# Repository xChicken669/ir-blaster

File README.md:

# 
IR blaster that runs on an esp32 c3 supermini It uses 4 push buttons, an IR led and an IR receiver
## why have I made this project??
I have always wanted to make an IR blaster from scratch but I didnt have the time and money to do so, now I am able to make it thanks to hackclub :).
## how did I make this project
- Autodesk Fusion 360 for CAD
- Kicad for pcb design
- Arduino IDE for firmware
## screenshots

also it uses two m2 screws for assembly and two m2 nuts.

## BOM
| Component                      | Qty | Link                                                                               | Price - CZK | Price  - USD |
|--------------------------------|-----|------------------------------------------------------------------------------------|-------------|--------------|
|  VISHAY TSAL6100 IR LED        | 1   | https://www.gme.cz/v/1486297/vishay-tsal6100-infracervena-led-5mm                  | 5           | 0.23         |
| DIOTEC BC337                   | 1   | https://www.gme.cz/v/1487096/diotec-bc337-40bk-bipolarni-tranzistor                | 0.85        | 0.0391       |
| Resistor 150ohms               | 1   | https://www.gme.cz/v/1494168/gym-cym-rm-150r-06w-1-0207-metalizovany-rezistor      | 4           | 0.184        |
| Resistor 1000ohms              | 1   | https://www.gme.cz/v/1486228/gym-cym-rm-1k-06w-1-0207-metalizovany-rezistor        | 4           | 0.184        |
| Esp32 C3 Supermini             | 1   | https://www.laskakit.cz/esp32-c3-super-mini-wifi-bluetooth-modul/                  | 148         | 6.808        |
| VISHAY TSOP3848 IR RECEIVER    | 1   | https://www.gme.cz/v/1489884/vishay-tsop4838-ir-prijimac                           | 18          | 0.828        |
| KLS TS6601-5.0-100 push button | 4   | https://www.gme.cz/v/1500825/kls-ts6601-50-100-mikrospinac                         | 2.8         | 0.1288       |
| 0.96" I2C OLED display 128x64  | 1   | https://www.gme.cz/v/1509095/oled-displej-096-128x64-i2c-bily                      | 100         | 4.6          |
| LiPol Battery                  | 1   | https://www.laskakit.cz/geb-lipol-baterie-302040-200mah-3-7v-jst-sh-2-0/#ratingTab | 70          | 3.22         |
| Tp4056 Battery charging module | 1   | https://www.laskakit.cz/nabijecka-li-ion-clanku-tp4056-s-ochranou-usb-c/           | 18          | 0.828        |
| PCB                            | 5   | https://jlcpcb.com                                                                 | 226.3043478 | 10.41        |
| Filament                       | 12g | Supplied by myself                                                                 | 4.8         | 0.2208       |

total = 601.75czk / 27.56usd
## AI
I used ai for a little bit of research for coding and for finding correct components

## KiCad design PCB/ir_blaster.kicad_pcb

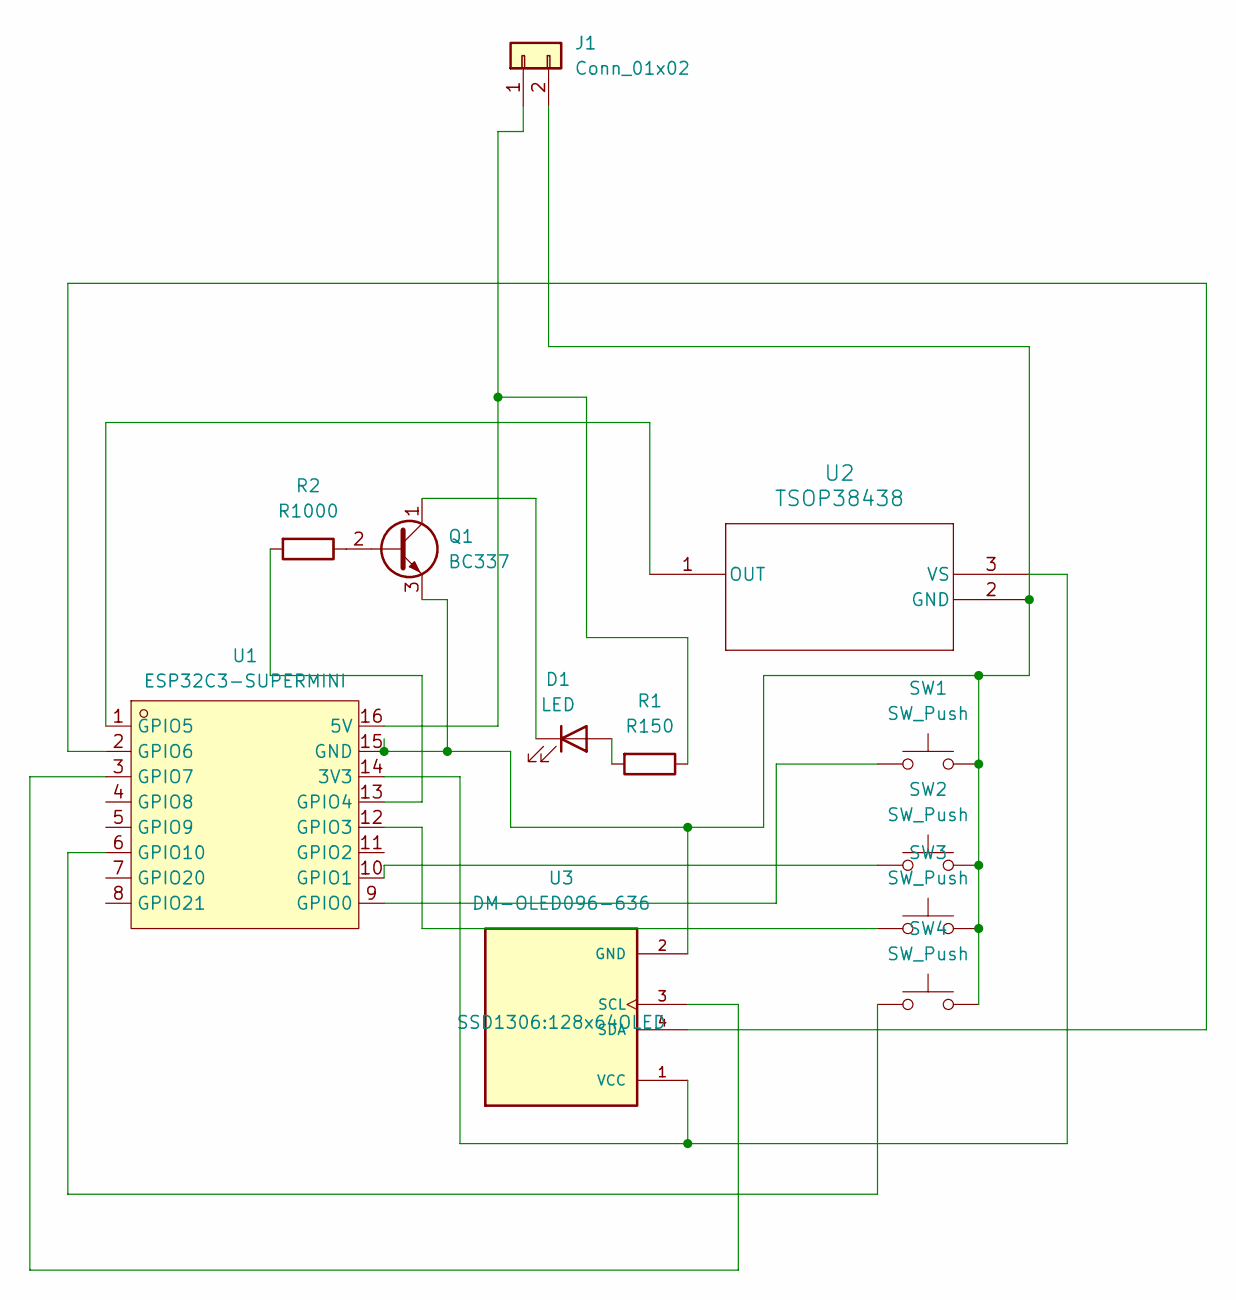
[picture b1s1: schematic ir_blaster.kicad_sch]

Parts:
D1: LED; LED_D5.0mm
J1: Conn_01x02; PinHeader_1x02_P2.54mm_Vertical
Q1: BC337; TO-92_Inline
R1: R150; R_Axial_DIN0207_L6.3mm_D2.5mm_P7.62mm_Horizontal
R2: R1000; R_Axial_DIN0207_L6.3mm_D2.5mm_P7.62mm_Horizontal
SW1, SW2, SW3, SW4: SW_Push; SW_PUSH_6mm_H5mm
U1: ESP32C3-SUPERMINI; esp32supermini; MPN ESP32C3-SuperMini; LCSC Part C9900147397
U2: TSOP38438; TSOP_4PIN_VIS
U3: DM-OLED096-636; 128x64OLED; PARTREV 2018-09-10

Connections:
unnamed: D1.2 (A), R1.2
unnamed: D1.1 (K), Q1.1 (C)
unnamed: J1.2 (GND), Q1.3 (E), SW1.2, SW2.2, SW3.2, SW4.2, U1.15 (GND), U2.2 (GND), U3.2 (GND)
unnamed: J1.1 (V), R1.1, U1.16 (5V)
unnamed: Q1.2 (B), R2.1
unnamed: U1.14 (3V3), U2.3 (VS), U3.1 (VCC)
unnamed: SW1.1, U1.9 (GPIO0)
unnamed: SW2.1, U1.10 (GPIO1)
unnamed: SW3.1, U1.12 (GPIO3)
unnamed: R2.2, U1.13 (GPIO4)
unnamed: U1.1 (GPIO5), U2.1 (OUT)
unnamed: U1.2 (GPIO6), U3.4 (SDA)
unnamed: U1.3 (GPIO7), U3.3 (SCL)
unnamed: SW4.1, U1.6 (GPIO10)

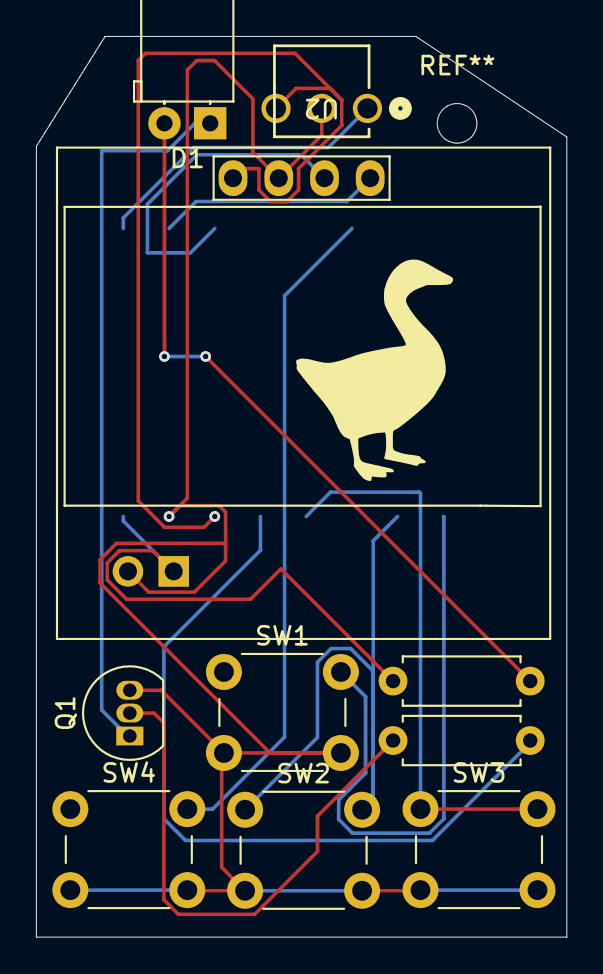
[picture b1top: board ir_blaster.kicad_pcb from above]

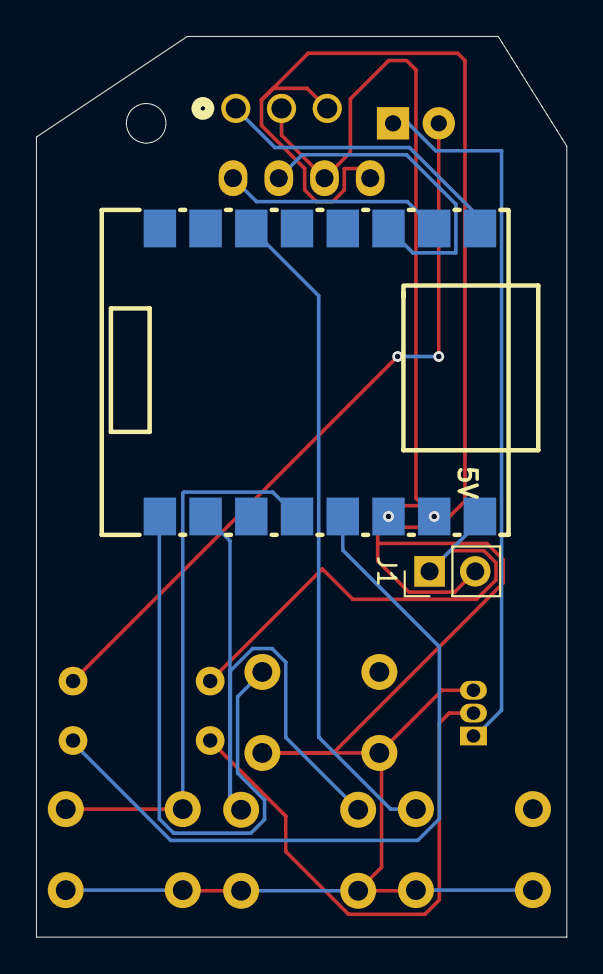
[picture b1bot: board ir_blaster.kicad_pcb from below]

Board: 2 copper layers, 29.5 x 50.0 mm, 12 parts (2 on the bottom side), 14 nets.
